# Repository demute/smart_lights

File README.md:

# smart_lights
This is a prototype for implementing smart lights: Lights that are saving
energy by selectively controlling which lights are on. The prototype is based
on the [Turtle Board from Radio Shuttle](https://www.radioshuttle.de/en/turtle-en/turtle-board-en/).
A radar motion detector has been added to the board, designed around the
cdm324 sensor, schematic and layout made in KiCAD and Inspired by
[limpkin](https://www.limpkin.fr/index.php?post/2017/02/22/Making-the-Electronics-for-a-24GHz-Doppler-Motion-Sensor).
The daughter board has one micro-usb connector for power and one usb-a connector
for a usb-lamp, which would be replaced with a zhaga socket on a real product.

The idea is this: Suppose luminaires are installed along a road and suppose
all luminaires are turned off. Now, if one luminaire detects motion, it will
lit itself up but also adjacent luminaires. Since adjacent luminaires are lit
up, the perceived feeling would be that the lights are on all the time.

The hardware for making this work looks like this:

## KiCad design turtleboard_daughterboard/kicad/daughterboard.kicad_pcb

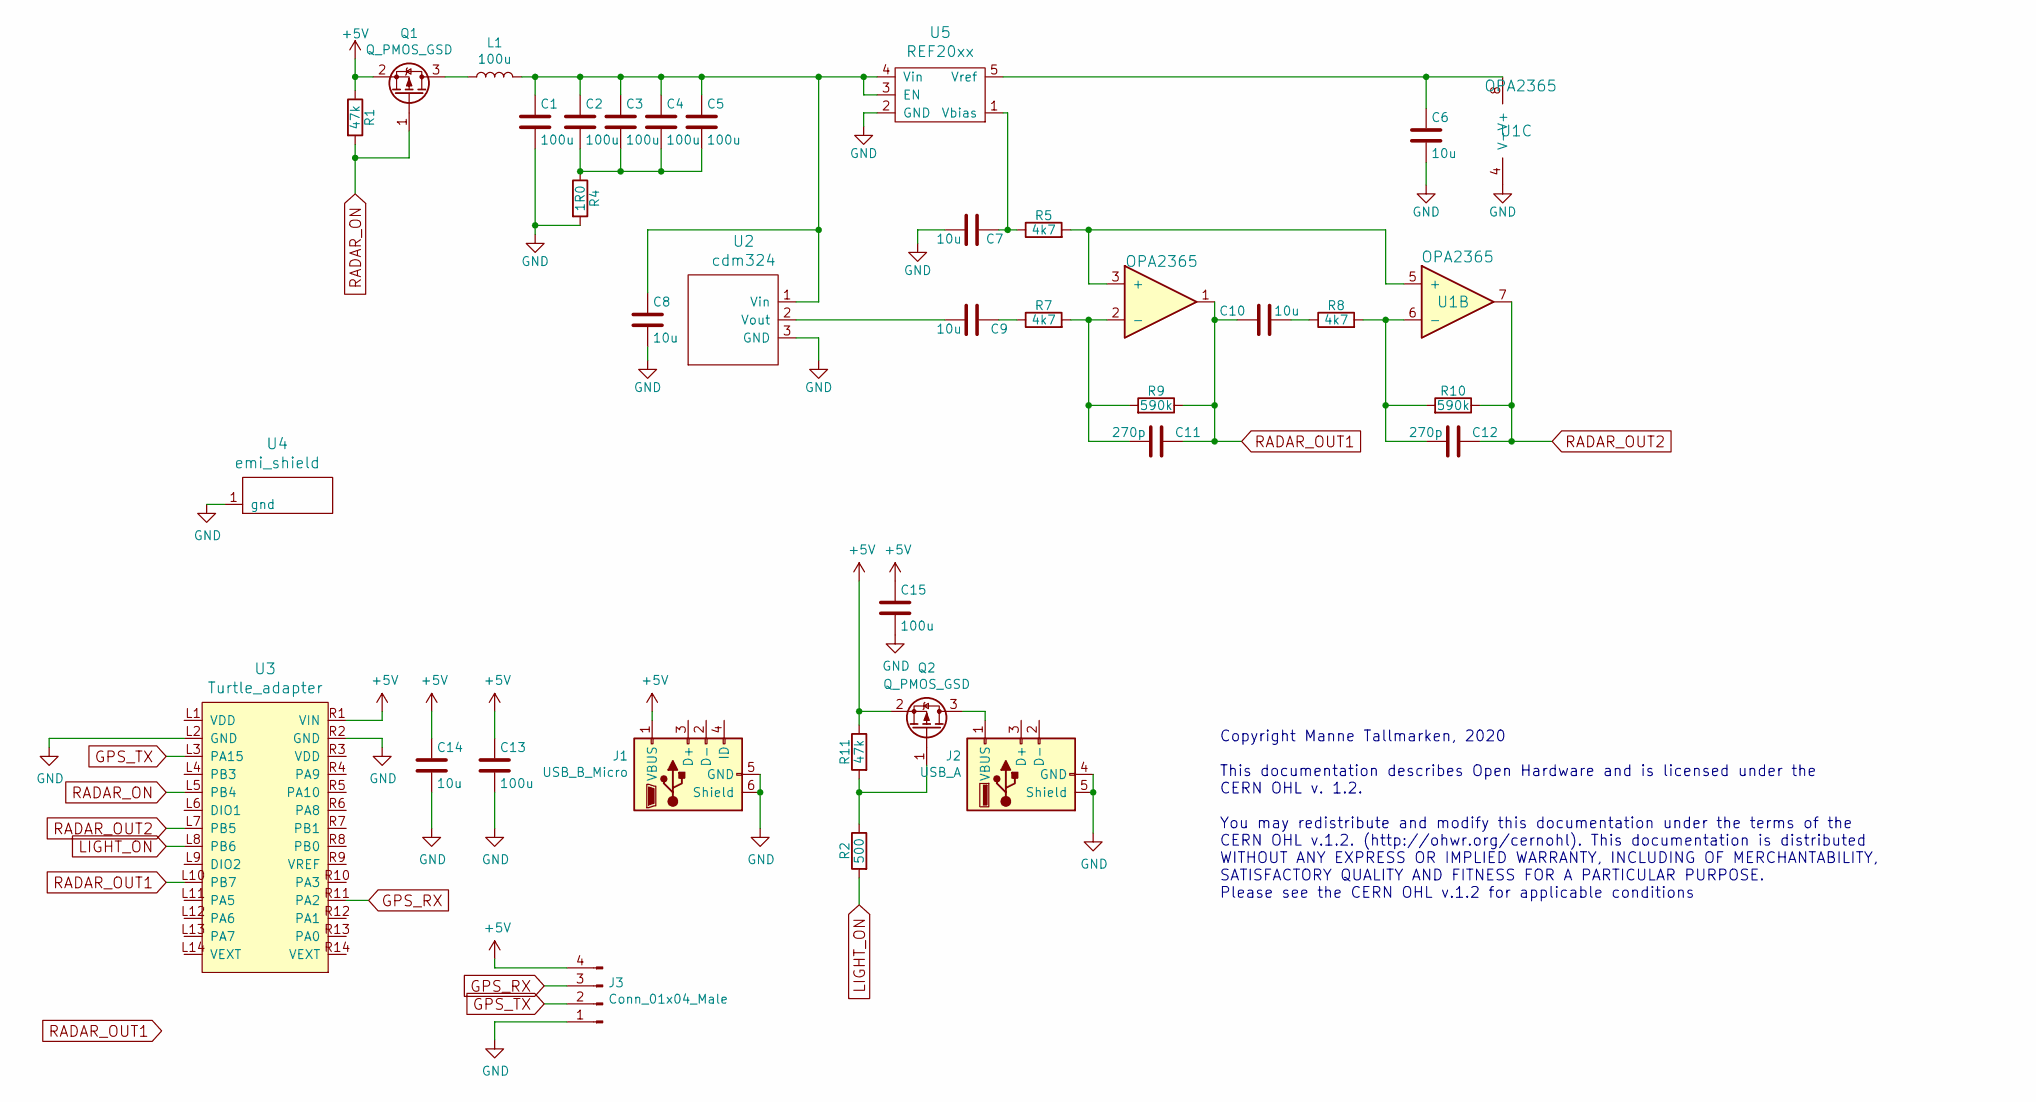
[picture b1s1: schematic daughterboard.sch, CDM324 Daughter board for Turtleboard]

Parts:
C1, C2, C3, C4, C5, C13, C15: 100u; C_1206_3216Metric_Pad1.42x1.75mm_HandSolder
C6, C7, C8, C9, C10, C14: 10u; C_0805_2012Metric
C11, C12: 270p; C_0603_1608Metric
J1: USB_B_Micro; usb-micro
J2: USB_A; usb-a
J3: Conn_01x04_Male; PinSocket_1x04_P2.54mm_Horizontal
L1: 100u; pa4319
Q1, Q2: Q_PMOS_GSD; SOT-23
R1, R11: 47k; R_0603_1608Metric
R2: 500; R_0603_1608Metric
R4: 1R0; R_0603_1608Metric
R5, R7, R8: 4k7; R_0603_1608Metric
R9, R10: 590k; R_0603_1608Metric
U1: OPA2365; SOIC-8_3.9x4.9mm_P1.27mm
U2: cdm324
U3: Turtle_adapter; turtleboard
U4: emi_shield; sms-202c
U5: REF20xx; SOT-23-5

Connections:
+5V: C13.1, C14.1, C15.1, J1.1 (VBUS), J3.4, Q1.2 (S), Q2.2 (S), R1.1, R11.1, U3.R1 (VIN)
GND: C1.2, C6.2, C7.2, C8.2, C13.2, C14.2, C15.2, J1.5 (GND), J1.6 (Shield), J2.4 (GND), J2.5 (Shield), J3.1, R4.2, U1.4 (V-), U2.3 (GND), U3.L2 (GND), U3.R2 (GND), U4.1, U5.2 (GND)
GPS_RX: J3.3, U3.R11 (PA2)
GPS_TX: J3.2, U3.L3 (PA15)
LIGHT_ON: R2.2, U3.L8 (PB6)
unnamed: C1.1, C2.1, C3.1, C4.1, C5.1, C8.1, L1.2, U2.1 (Vin), U5.3 (EN), U5.4 (Vin)
unnamed: C2.2, C3.2, C4.2, C5.2, R4.1
unnamed: C6.1, U1.8 (V+), U5.5 (Vref)
unnamed: C7.1, R5.1, U5.1 (Vbias)
unnamed: C9.1, R7.1
unnamed: C9.2, U2.2 (Vout)
unnamed: C10.2, R8.1
unnamed: C11.2, R7.2, R9.2, U1.2 (-)
unnamed: C12.2, R8.2, R10.2, U1.6 (-)
unnamed: J2.1 (VBUS), Q2.3 (D)
unnamed: L1.1, Q1.3 (D)
unnamed: Q2.1 (G), R2.1, R11.2
unnamed: R5.2, U1.3 (+), U1.5 (+)
RADAR_ON: Q1.1 (G), R1.2, U3.L5 (PB4)
RADAR_OUT1: C10.1, C11.1, R9.1, U1.1, U3.L10 (PB7)
RADAR_OUT2: C12.1, R10.1, U1.7, U3.L7 (PB5)

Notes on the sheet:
Copyright Manne Tallmarken, 2020 This documentation describes Open Hardware and is licensed under the CERN OHL v. 1.2. You may redistribute and modify this documentation under the terms of the CERN OHL v.1.2. (http://ohwr.org/cernohl). This documentation is distributed WITHOUT ANY EXPRESS OR IMPLIE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

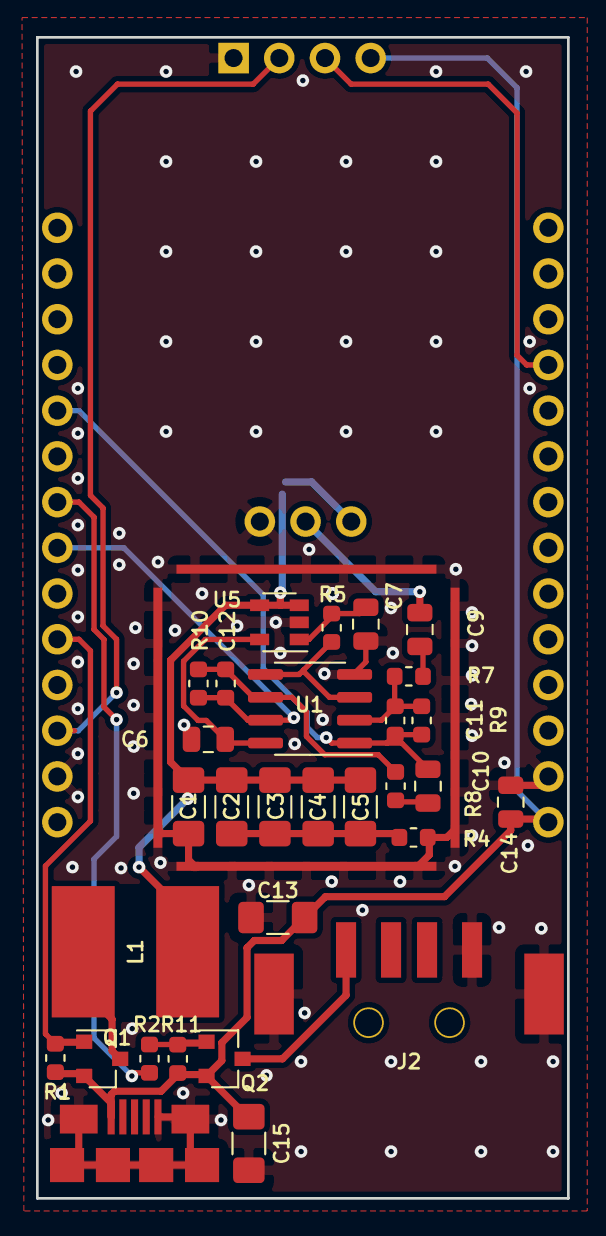
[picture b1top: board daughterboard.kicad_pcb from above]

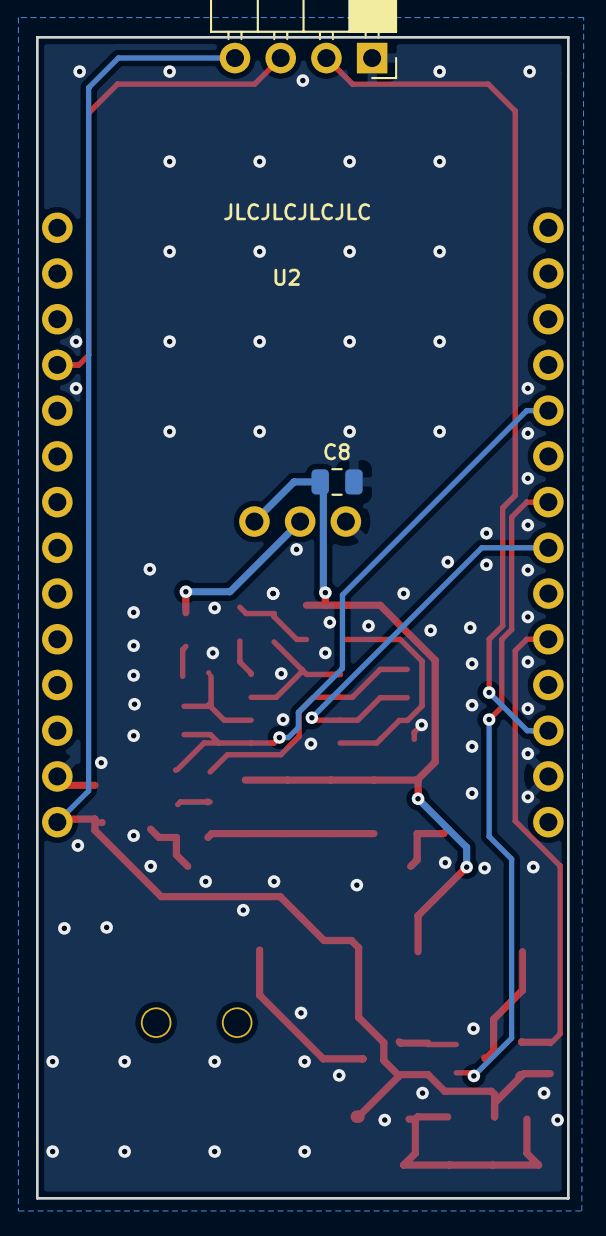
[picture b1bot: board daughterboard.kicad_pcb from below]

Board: 4 copper layers, 29.5 x 64.5 mm, 35 parts (4 on the bottom side), 21 nets.

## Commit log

2021-02-02 add gitignore
2021-02-02 add street picture
2021-02-02 add picture of hardware
2021-02-02 add firmware
2021-02-02 fixed typo
2021-02-02 add kicad files
2021-02-24 better state handling, improved stability for sending and receiving messages, improved detection algorithm
